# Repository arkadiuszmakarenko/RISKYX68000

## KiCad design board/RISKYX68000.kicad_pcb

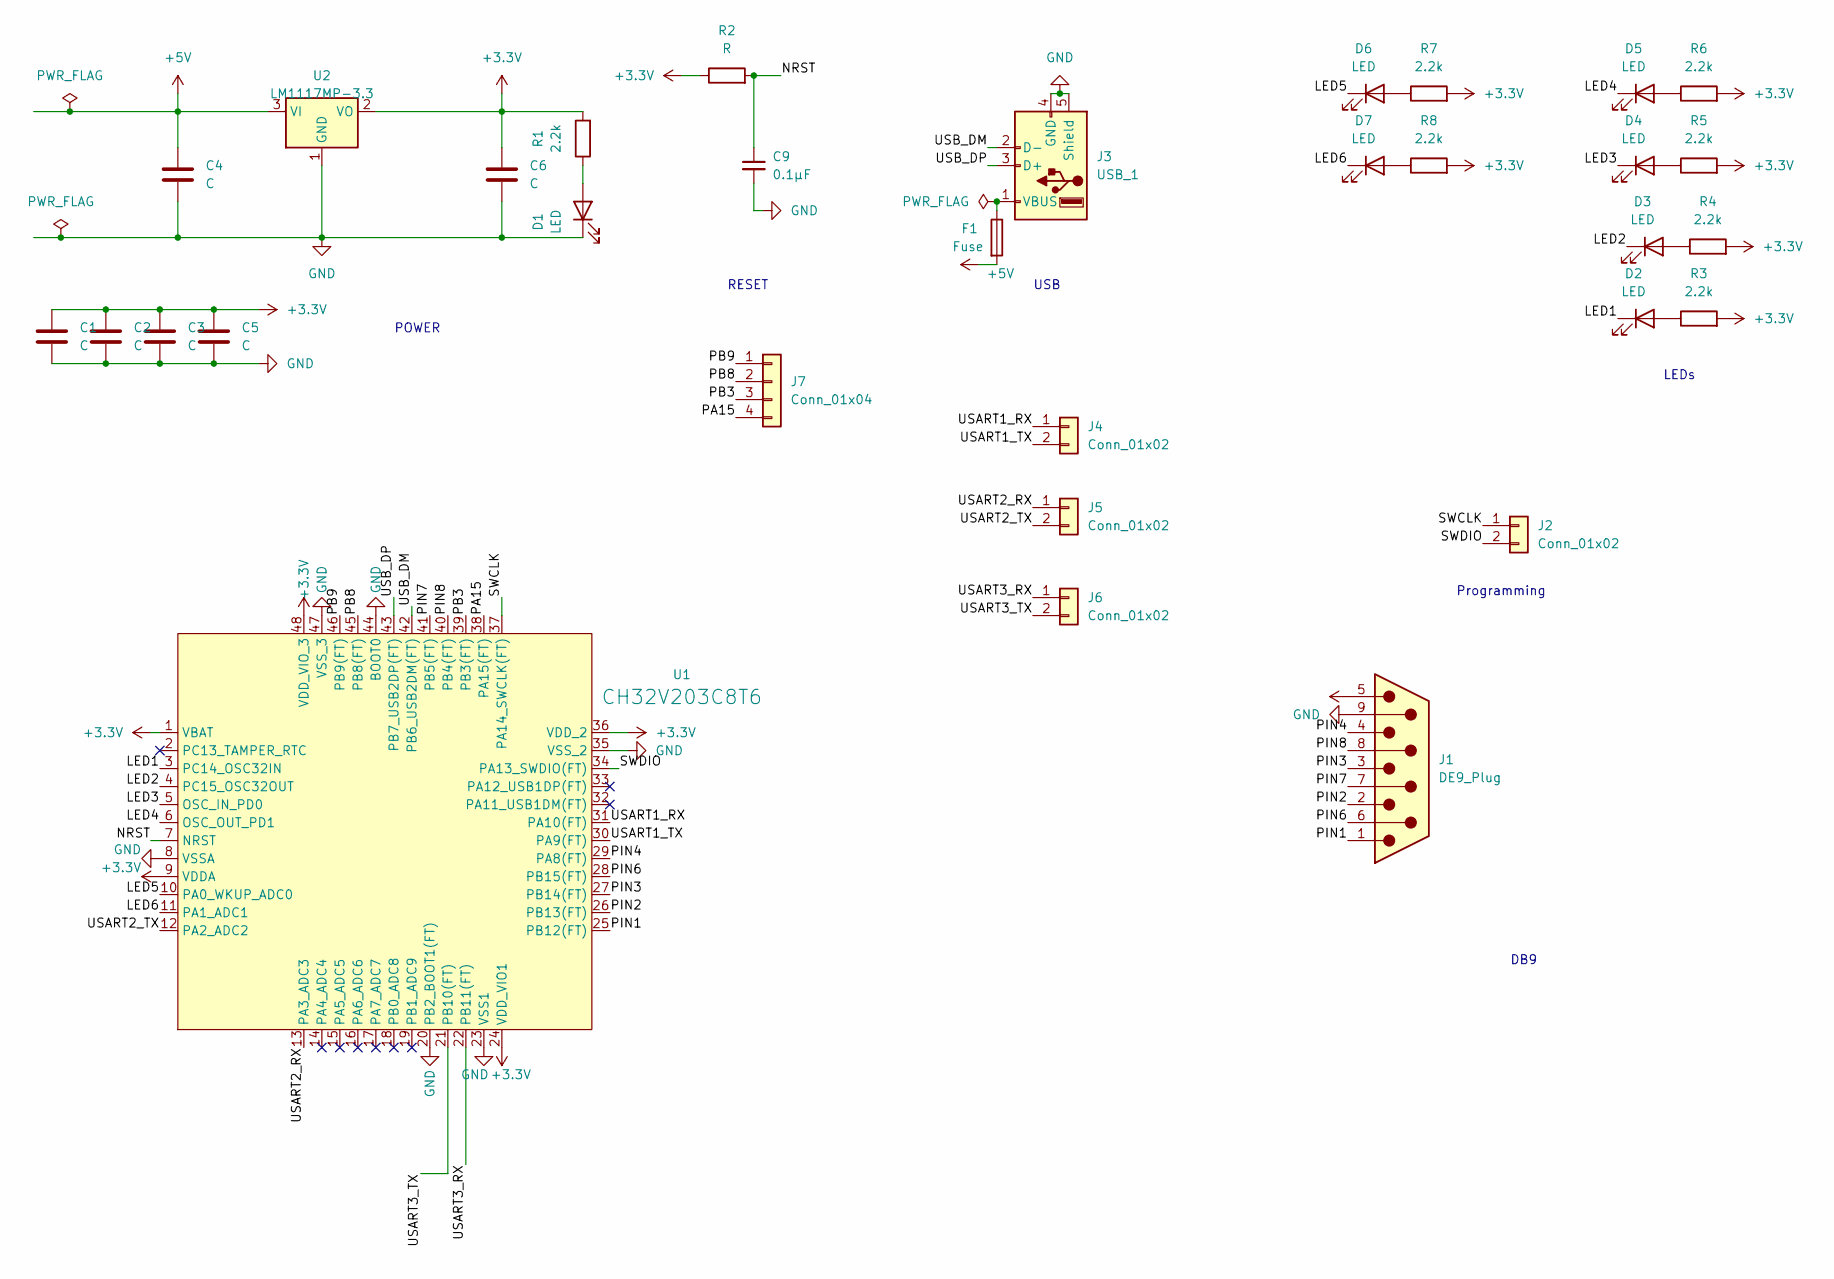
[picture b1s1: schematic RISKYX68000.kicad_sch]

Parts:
C1, C2, C3, C4, C5, C6: C; C_0603_1608Metric_Pad1.08x0.95mm_HandSolder
C9: 0.1μF; C_0603_1608Metric_Pad1.08x0.95mm_HandSolder; LCSC C14663
D1, D2, D3, D4, D5, D6, D7: LED; LED_0805_2012Metric_Pad1.15x1.40mm_HandSolder
F1: Fuse; Fuse_1206_3216Metric_Pad1.42x1.75mm_HandSolder
J1: DE9_Plug; DSUB-9_Pins_EdgeMount_P2.77mm
J2, J4, J5, J6: Conn_01x02; PinHeader_1x02_P2.54mm_Vertical
J3: USB_1; USB_A_Connfly_DS1095
J7: Conn_01x04; PinHeader_1x04_P2.54mm_Vertical
R1, R3, R4, R5, R6, R7, R8: 2.2k; R_0603_1608Metric_Pad0.98x0.95mm_HandSolder
R2: R; R_0603_1608Metric_Pad0.98x0.95mm_HandSolder
U1: CH32V203C8T6; LQFP-48_7x7mm_P0.5mm
U2: LM1117MP-3.3; SOT-89-3

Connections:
+3.3V: C1.1, C2.1, C3.1, C5.1, C6.1, R1.2, R2.1, R3.2, R4.2, R5.2, R6.2, R7.2, R8.2, U1.1 (VBAT), U1.9 (VDDA), U1.24 (VDD_VIO1), U1.36 (VDD_2), U1.48 (VDD_VIO_3), U2.2 (VO)
+5V: C4.1, F1.2, J1.5, U2.3 (VI)
/LED1: D2.1 (K), U1.3 (PC14_OSC32IN)
/LED2: D3.1 (K), U1.4 (PC15_OSC32OUT)
/LED3: D4.1 (K), U1.5 (OSC_IN_PD0)
/LED4: D5.1 (K), U1.6 (OSC_OUT_PD1)
/LED5: D6.1 (K), U1.10 (PA0_WKUP_ADC0)
/LED6: D7.1 (K), U1.11 (PA1_ADC1)
/NRST: C9.1, R2.2, U1.7 (NRST)
/PA15: J7.4, U1.38 (PA15(FT))
/PB3: J7.3, U1.39 (PB3(FT))
/PB8: J7.2, U1.45 (PB8(FT))
/PB9: J7.1, U1.46 (PB9(FT))
/PIN1: J1.1, U1.25 (PB12(FT))
/PIN2: J1.2, U1.26 (PB13(FT))
/PIN3: J1.3, U1.27 (PB14(FT))
/PIN4: J1.4, U1.29 (PA8(FT))
/PIN6: J1.6, U1.28 (PB15(FT))
/PIN7: J1.7, U1.41 (PB5(FT))
/PIN8: J1.8, U1.40 (PB4(FT))
/SWCLK: J2.1, U1.37 (PA14_SWCLK(FT))
/SWDIO: J2.2, U1.34 (PA13_SWDIO(FT))
/USART1_RX: J4.1, U1.31 (PA10(FT))
/USART1_TX: J4.2, U1.30 (PA9(FT))
/USART2_RX: J5.1, U1.13 (PA3_ADC3)
/USART2_TX: J5.2, U1.12 (PA2_ADC2)
/USART3_RX: J6.1, U1.22 (PB11(FT))
/USART3_TX: J6.2, U1.21 (PB10(FT))
/USB_DM: J3.2 (D-), U1.42 (PB6_USB2DM(FT))
/USB_DP: J3.3 (D+), U1.43 (PB7_USB2DP(FT))
GND: C1.2, C2.2, C3.2, C4.2, C5.2, C6.2, C9.2, D1.1 (K), J1.9, J3.4 (GND), J3.5 (Shield), U1.8 (VSSA), U1.20 (PB2_BOOT1(FT)), U1.23 (VSS1), U1.35 (VSS_2), U1.44 (BOOT0), U1.47 (VSS_3), U2.1 (GND)
unnamed: D1.2 (A), R1.1
unnamed: D2.2 (A), R3.1
unnamed: D3.2 (A), R4.1
unnamed: D4.2 (A), R5.1
unnamed: D5.2 (A), R6.1
unnamed: D6.2 (A), R7.1
unnamed: D7.2 (A), R8.1
unnamed: F1.1, J3.1 (VBUS)

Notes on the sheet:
USB
LEDs
Programming
POWER
DB9
RESET

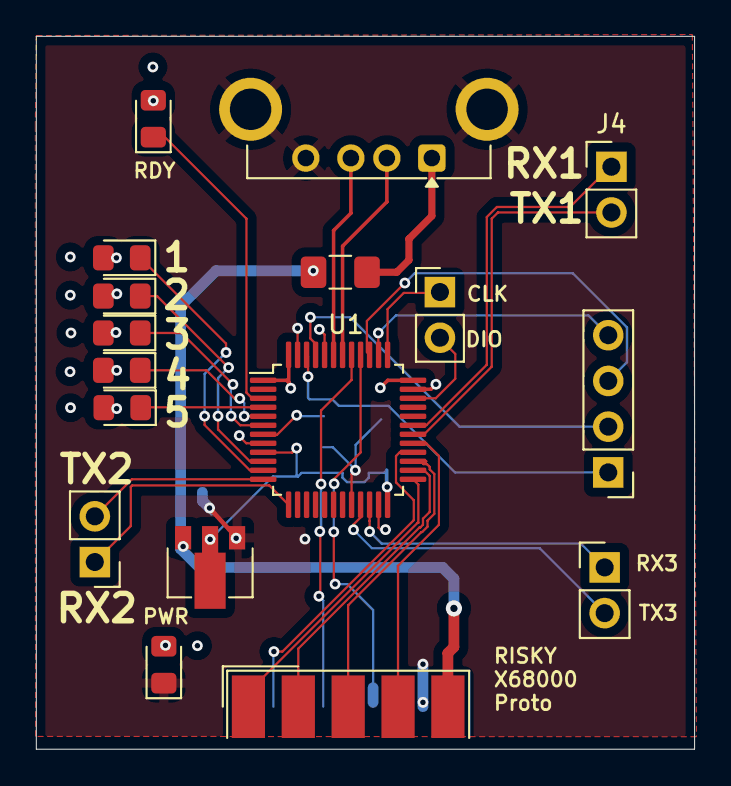
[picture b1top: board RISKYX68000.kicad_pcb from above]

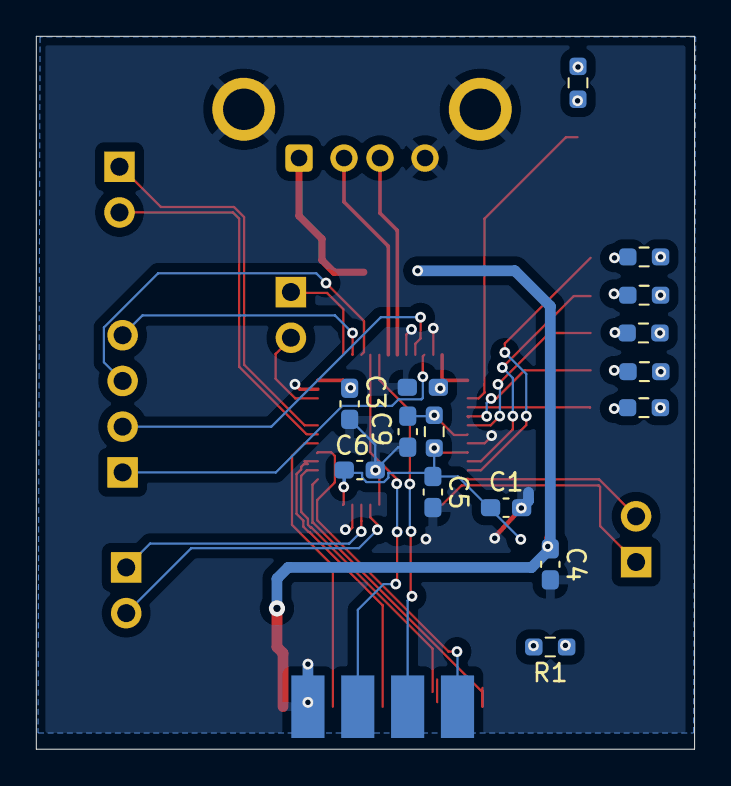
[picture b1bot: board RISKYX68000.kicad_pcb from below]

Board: 4 copper layers, 36.6 x 39.6 mm, 32 parts (15 on the bottom side), 39 nets.

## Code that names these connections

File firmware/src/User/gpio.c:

#include "gpio.h"
#include "ch32v20x_exti.h"

void GPIO_Config()
{

    //Reset RCC
    GPIO_DeInit(GPIOA);

    RCC_APB2PeriphClockCmd(RCC_APB2Periph_GPIOA, ENABLE);
    RCC_APB2PeriphClockCmd(RCC_APB2Periph_GPIOB, ENABLE);
    RCC_APB2PeriphClockCmd(RCC_APB2Periph_GPIOC, ENABLE);
    RCC_APB2PeriphClockCmd(RCC_APB2Periph_GPIOD, ENABLE);
    RCC_APB2PeriphClockCmd(RCC_APB2Periph_AFIO, ENABLE);

    // Disconnect PD0/PD1 from the HSE oscillator pads so they can be driven as GPIO
    GPIO_PinRemapConfig(GPIO_Remap_PD01, ENABLE);

    GPIO_InitTypeDef GPIO_InitStructure = {0};


    /*Configure GPIO pin Output Level */
    GPIO_WriteBit(LED_GPIO_Port,LED_Pin, Bit_SET);

    GPIO_WriteBit(LED1_GPIO_Port,LED1_Pin, Bit_SET);
    GPIO_WriteBit(LED2_GPIO_Port,LED2_Pin, Bit_SET);
    GPIO_WriteBit(LED3_GPIO_Port,LED3_Pin, Bit_SET);
    GPIO_WriteBit(LED4_GPIO_Port,LED4_Pin, Bit_SET);
    GPIO_WriteBit(LED5_GPIO_Port,LED5_Pin, Bit_SET);

    // DE-9
    GPIO_WriteBit(UP_GPIO_Port, UP_Pin, Bit_SET);
    GPIO_WriteBit(DN_GPIO_Port, DN_Pin, Bit_SET);
    GPIO_WriteBit(LT_GPIO_Port, LT_Pin, Bit_SET);
    GPIO_WriteBit(RT_GPIO_Port, RT_Pin, Bit_SET);
    GPIO_WriteBit(B1_GPIO_Port, B1_Pin, Bit_SET);
    GPIO_WriteBit(B2_GPIO_Port, B2_Pin, Bit_SET);

    // GPIO_WriteBit(KBD_DATA_GPIO_Port, KBD_DATA_Pin, Bit_SET);
    // GPIO_WriteBit(KBD_CLOCK_GPIO_Port, KBD_CLOCK_Pin,Bit_SET);
    // GPIO_WriteBit(KB_RESET_GPIO_Port,KB_RESET_GPIO_Pin,Bit_SET);

    GPIO_WriteBit(GPIOA,GPIO_Pin_13,Bit_RESET);
    GPIO_WriteBit(GPIOA,GPIO_Pin_14,Bit_RESET);



    /*Configure GPIO pins : PCPin PCPin PCPin */
    GPIO_InitStructure.GPIO_Pin = LED_Pin;
    GPIO_InitStructure.GPIO_Mode = GPIO_Mode_Out_PP;
    GPIO_InitStructure.GPIO_Speed = GPIO_Speed_50MHz;
    GPIO_Init(LED_GPIO_Port, &GPIO_InitStructure);

    GPIO_InitStructure.GPIO_Pin = LED1_Pin;
    GPIO_Init(LED1_GPIO_Port, &GPIO_InitStructure);
    GPIO_InitStructure.GPIO_Pin = LED2_Pin;
    GPIO_Init(LED2_GPIO_Port, &GPIO_InitStructure);
    GPIO_InitStructure.GPIO_Pin = LED3_Pin;
    GPIO_Init(LED3_GPIO_Port, &GPIO_InitStructure);
    GPIO_InitStructure.GPIO_Pin = LED4_Pin;
    GPIO_Init(LED4_GPIO_Port, &GPIO_InitStructure);
    GPIO_InitStructure.GPIO_Pin = LED5_Pin;
    GPIO_Init(LED5_GPIO_Port, &GPIO_InitStructure);

    GPIO_InitStructure.GPIO_Pin = B1_Pin;
    GPIO_InitStructure.GPIO_Mode = GPIO_Mode_Out_PP;
    GPIO_InitStructure.GPIO_Speed = GPIO_Speed_50MHz;
    GPIO_Init(B1_GPIO_Port, &GPIO_InitStructure);

    GPIO_InitStructure.GPIO_Pin = B2_Pin;
    GPIO_InitStructure.GPIO_Mode = GPIO_Mode_Out_PP;
    GPIO_InitStructure.GPIO_Speed = GPIO_Speed_50MHz;
    GPIO_Init(B2_GPIO_Port, &GPIO_InitStructure);

    GPIO_InitStructure.GPIO_Pin = UP_Pin;
    GPIO_InitStructure.GPIO_Mode = GPIO_Mode_Out_PP;
    GPIO_InitStructure.GPIO_Speed = GPIO_Speed_50MHz;
    GPIO_Init(UP_GPIO_Port, &GPIO_InitStructure);

    GPIO_InitStructure.GPIO_Pin = DN_Pin;
    GPIO_InitStructure.GPIO_Mode = GPIO_Mode_Out_PP;
    GPIO_InitStructure.GPIO_Speed = GPIO_Speed_50MHz;
    GPIO_Init(DN_GPIO_Port, &GPIO_InitStructure);

    GPIO_InitStructure.GPIO_Pin = LT_Pin;
    GPIO_InitStructure.GPIO_Mode = GPIO_Mode_Out_PP;
    GPIO_InitStructure.GPIO_Speed = GPIO_Speed_50MHz;
    GPIO_Init(LT_GPIO_Port, &GPIO_InitStructure);

    GPIO_InitStructure.GPIO_Pin = RT_Pin;
    GPIO_InitStructure.GPIO_Mode = GPIO_Mode_Out_PP;
    GPIO_InitStructure.GPIO_Speed = GPIO_Speed_50MHz;
    GPIO_Init(RT_GPIO_Port, &GPIO_InitStructure);

    // STROBE input (from X68000)
    GPIO_InitStructure.GPIO_Pin = STROBE_Pin;
    GPIO_InitStructure.GPIO_Mode = GPIO_Mode_IN_FLOATING;
    GPIO_InitStructure.GPIO_Speed = GPIO_Speed_50MHz;
    GPIO_Init(STROBE_GPIO_Port, &GPIO_InitStructure);

    // READY input (pull-up) - PB9
    GPIO_InitStructure.GPIO_Pin = RDY_Pin;
    GPIO_InitStructure.GPIO_Mode = GPIO_Mode_IPU;
    GPIO_InitStructure.GPIO_Speed = GPIO_Speed_50MHz;
    GPIO_Init(RDY_GPIO_Port, &GPIO_InitStructure);

    // MSCTRL input (pull-up) - PB8
    GPIO_InitStructure.GPIO_Pin = MSCTRL_Pin;
    GPIO_InitStructure.GPIO_Mode = GPIO_Mode_IPU;
    GPIO_InitStructure.GPIO_Speed = GPIO_Speed_50MHz;
    GPIO_Init(MSCTRL_GPIO_Port, &GPIO_InitStructure);

    // Configure EXTI interrupts for READY (PB9) and MSCTRL (PB8)
    EXTI_InitTypeDef EXTI_InitStructure = {0};
    NVIC_InitTypeDef NVIC_InitStructure = {0};

    // READY (PB9) - EXTI9: falling and rising edge
    GPIO_EXTILineConfig(GPIO_PortSourceGPIOB, GPIO_PinSource9);
    EXTI_InitStructure.EXTI_Line = EXTI_Line9;
    EXTI_InitStructure.EXTI_Mode = EXTI_Mode_Interrupt;
    EXTI_InitStructure.EXTI_Trigger = EXTI_Trigger_Rising_Falling;
    EXTI_InitStructure.EXTI_LineCmd = ENABLE;
    EXTI_Init(&EXTI_InitStructure);

    // MSCTRL (PB8) - EXTI8: falling edge
    GPIO_EXTILineConfig(GPIO_PortSourceGPIOB, GPIO_PinSource8);
    EXTI_InitStructure.EXTI_Line = EXTI_Line8;
    EXTI_InitStructure.EXTI_Mode = EXTI_Mode_Interrupt;
    EXTI_InitStructure.EXTI_Trigger = EXTI_Trigger_Falling;
    EXTI_InitStructure.EXTI_LineCmd = ENABLE;
    EXTI_Init(&EXTI_InitStructure);

    // Enable EXTI9_5 IRQ (covers EXTI lines 5-9, including both PB8 and PB9)
    NVIC_InitStructure.NVIC_IRQChannel = EXTI9_5_IRQn;
    NVIC_InitStructure.NVIC_IRQChannelPreemptionPriority = 1;
    NVIC_InitStructure.NVIC_IRQChannelSubPriority = 1;
    NVIC_InitStructure.NVIC_IRQChannelCmd = ENABLE;
    NVIC_Init(&NVIC_InitStructure);

    // SWD pins - why to we configure them?
    GPIO_InitStructure.GPIO_Pin = GPIO_Pin_14;
    GPIO_InitStructure.GPIO_Mode = GPIO_Mode_Out_OD;
    GPIO_Init(GPIOA, &GPIO_InitStructure);

    GPIO_InitStructure.GPIO_Pin = GPIO_Pin_13;
    GPIO_InitStructure.GPIO_Mode = GPIO_Mode_Out_OD;
    GPIO_Init(GPIOA, &GPIO_InitStructure);




#if 0 // amiga mouse wheel
       //NVIC EXTI IRQ setup

    //MOUSE PIN 5 - MMB setup for Scroll support
    //On this PCB it is Port B Pin 10

	EXTI_InitTypeDef EXTI_InitStructure = {0};
	NVIC_InitTypeDef NVIC_InitStructure = {0};

	RCC_APB2PeriphClockCmd(RCC_APB2Periph_AFIO, ENABLE);
	RCC_APB2PeriphClockCmd(RCC_APB2Periph_GPIOB, ENABLE);

	GPIO_InitStructure.GPIO_Pin = MB_Pin;
	GPIO_InitStructure.GPIO_Mode = GPIO_Mode_IPU;
	GPIO_Init(MB_GPIO_Port, &GPIO_InitStructure);

	GPIO_EXTILineConfig(GPIO_PortSourceGPIOB, GPIO_PinSource10);
	EXTI_InitStructure.EXTI_Line = EXTI_Line10;
	EXTI_InitStructure.EXTI_Mode = EXTI_Mode_Interrupt;
	EXTI_InitStructure.EXTI_Trigger = EXTI_Trigger_Falling;
	EXTI_InitStructure.EXTI_LineCmd = ENABLE;
	EXTI_Init(&EXTI_InitStructure);

	NVIC_InitStructure.NVIC_IRQChannel = EXTI15_10_IRQn;
	NVIC_InitStructure.NVIC_IRQChannelPreemptionPriority = 1;
	NVIC_InitStructure.NVIC_IRQChannelSubPriority = 1;
	NVIC_InitStructure.NVIC_IRQChannelCmd = ENABLE;
	NVIC_Init(&NVIC_InitStructure);
#endif
}

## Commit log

2025-10-18 init project
2025-10-18 First PCB order
2025-11-07 keyboard and mouse works
2025-11-10 disabled key-inhibit for now
2025-11-10 remapped gamepad inputs
2026-05-10 wire up the 5 keyboard LEDs and drive them from kbd LED state
2026-05-12 document miniDIN pin mapping for keyboard/mouse UARTs
